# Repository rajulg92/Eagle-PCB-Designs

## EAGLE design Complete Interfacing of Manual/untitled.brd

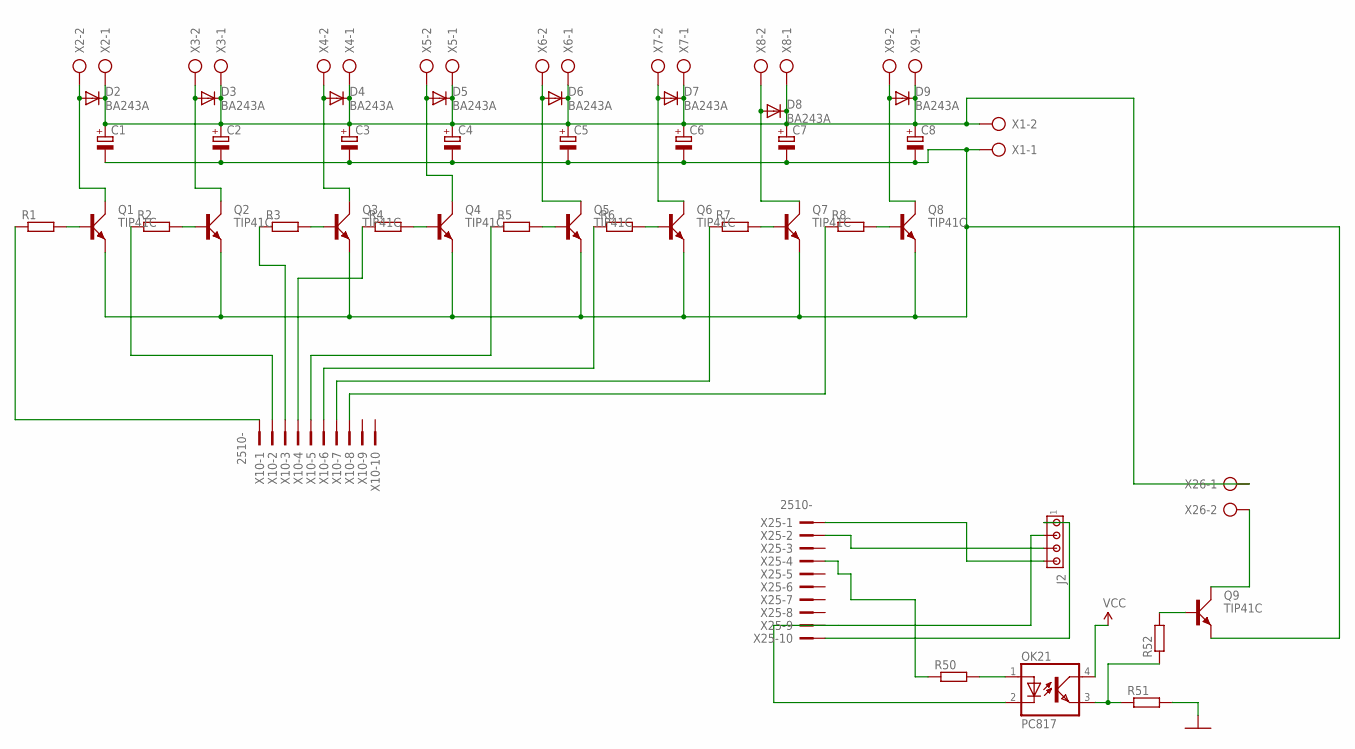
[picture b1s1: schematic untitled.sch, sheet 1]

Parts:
C1, C2, C3, C4, C5, C6, C7, C8: CPOL-EUE5-10.5; E5-10,5
D2, D3, D4, D5, D6, D7, D8, D9: BA243A; DO35-10
J2: MTA04-100; 10X04MTA
OK21: PC817; DIL04
Q1, Q2, Q3, Q4, Q5, Q6, Q7, Q8, Q9: TIP41C; TO220AV
R1, R2, R3, R4, R5, R6, R7, R8, R50, R51, R52: R-EU_0204/7; 0204/7
X1, X2, X3, X4, X5, X6, X7, X8, X9, X26: AK300/2
X10, X25: 2510-; PAK100/2500-10

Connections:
GND: R51.2; also elsewhere on the board
unnamed: Q1.B, R1.2
unnamed: Q2.B, R2.2
unnamed: Q3.B, R3.2
unnamed: Q4.B, R4.2
unnamed: Q5.B, R5.2
unnamed: Q7.B, R7.2
unnamed: Q8.B, R8.2
unnamed: Q6.B, R6.2
unnamed: D2.A, Q1.C, X2.2
unnamed: D3.A, Q2.C, X3.2
unnamed: D4.A, Q3.C, X4.2
unnamed: D5.A, Q4.C, X5.2
unnamed: D6.A, Q5.C, X6.2
unnamed: D7.A, Q6.C, X7.2
unnamed: D8.A, Q7.C, X8.2
unnamed: D9.A, Q8.C, X9.2
unnamed: C1.+, C2.+, C3.+, C4.+, C5.+, C6.+, C7.+, C8.+, D2.C, D3.C, D4.C, D5.C, D6.C, D7.C, D8.C, D9.C, X1.2, X2.1, X3.1, X4.1, X5.1, X6.1, X7.1, X8.1, X9.1, X26.1
unnamed: R3.1, X10.3
unnamed: R4.1, X10.4
unnamed: R1.1, X10.1
unnamed: R2.1, X10.2
unnamed: R5.1, X10.5
unnamed: R6.1, X10.6
unnamed: R7.1, X10.7
unnamed: R8.1, X10.8
unnamed: J2.1, X25.10
unnamed: J2.2, OK21.2 (C), X25.9
unnamed: J2.3, X25.2
unnamed: J2.4, X25.1
unnamed: OK21.1 (A), R50.2
unnamed: R50.1, X25.4
unnamed: OK21.3 (EMIT), R51.1, R52.1
unnamed: Q9.B, R52.2
unnamed: Q9.C, X26.2
unnamed: C1.-, C2.-, C3.-, C4.-, C5.-, C6.-, C7.-, C8.-, Q1.E, Q2.E, Q3.E, Q4.E, Q5.E, Q6.E, Q7.E, Q8.E, Q9.E, X1.1
VCC: OK21.4 (COL); also elsewhere on the board

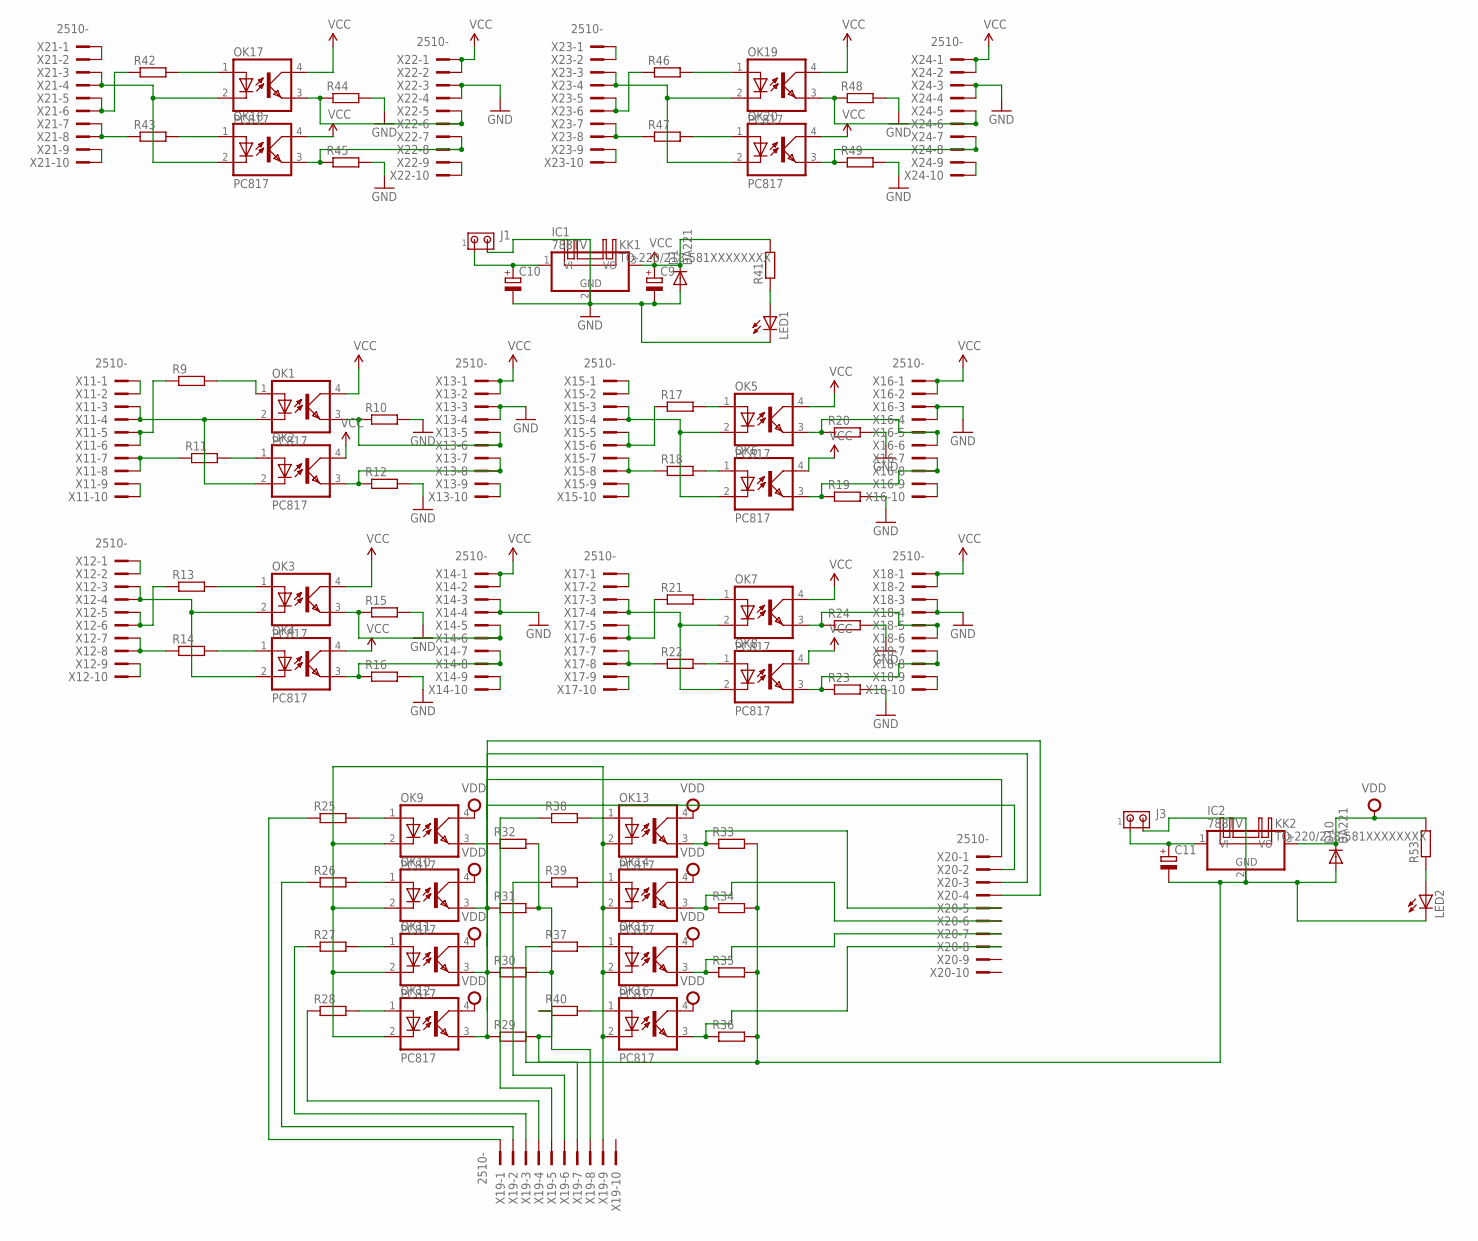
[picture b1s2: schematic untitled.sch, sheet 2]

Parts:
C9: CPOL-EUE5-10.5; E5-10,5
C10, C11: CPOL-EUE7.5-18; E7,5-18
D1, D10: BA221; DO35-10
IC1, IC2: 788TV; TO220V
J1, J3: MTA02-156; 1X2MTA
KK1, KK2: TO-220/218-581XXXXXXXX; 581XXXXXXXX
LED1, LED2: LEDSFH480; SFH480
OK1, OK2, OK3, OK4, OK5, OK6, OK7, OK8, OK9, OK10, OK11, OK12, OK13, OK14, OK15, OK16, OK17, OK18, OK19, OK20: PC817; DIL04; MPN PC817X4J000F
R9, R10, R11, R12, R13, R14, R15, R16, R17, R18, R19, R20, R21, R22, R23, R24, R25, R26, R27, R28, R29, R30, R31, R32, R33, R34, R35, R36, R37, R38, R39, R40, R41, R42, R43, R44, R45, R46, R47, R48, R49, R53: R-EU_0207/10; 0207/10
X11, X12, X13, X14, X15, X16, X17, X18, X19, X20, X21, X22, X23, X24: 2510-; PAK100/2500-10

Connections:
GND: C9.-, C10.-, D1.A, IC1.2 (GND), J1.2, LED1.K (C), R10.2, R12.2, R15.2, R16.2, R19.2, R20.2, R23.2, R24.2, R44.2, R45.2, R48.2, R49.2, X13.3, X13.4, X14.3, X14.4, X16.3, X16.4, X18.3, X18.4, X22.3, X22.4, X24.3, X24.4; also elsewhere on the board
unnamed: X11.1, X11.2
unnamed: R9.1, X11.5, X11.6
unnamed: R11.1, X11.7, X11.8
unnamed: X11.9, X11.10
unnamed: X12.1, X12.2
unnamed: R13.1, X12.5, X12.6
unnamed: R14.1, X12.7, X12.8
unnamed: X12.9, X12.10
unnamed: OK1.1 (A), R9.2
unnamed: OK2.1 (A), R11.2
unnamed: OK1.2 (C), OK2.2 (C), X11.3, X11.4
unnamed: OK2.3 (EMIT), R12.1, X13.7, X13.8
unnamed: X13.9, X13.10
unnamed: OK3.1 (A), R13.2
unnamed: OK4.1 (A), R14.2
unnamed: OK3.2 (C), OK4.2 (C), X12.3, X12.4
unnamed: OK3.3 (EMIT), R15.1, X14.5, X14.6
unnamed: OK4.3 (EMIT), R16.1, X14.7, X14.8
unnamed: X14.9, X14.10
unnamed: OK5.1 (A), R17.2
unnamed: OK6.1 (A), R18.2
unnamed: X15.1, X15.2
unnamed: R17.1, X15.5, X15.6
unnamed: R18.1, X15.7, X15.8
unnamed: X15.9, X15.10
unnamed: OK5.2 (C), OK6.2 (C), X15.3, X15.4
unnamed: OK5.3 (EMIT), R20.1, X16.5, X16.6
unnamed: OK6.3 (EMIT), R19.1, X16.7, X16.8
unnamed: X16.9, X16.10
unnamed: OK7.1 (A), R21.2
unnamed: OK8.1 (A), R22.2
unnamed: X17.1, X17.2
unnamed: R21.1, X17.5, X17.6
unnamed: R22.1, X17.7, X17.8
unnamed: X17.9, X17.10
unnamed: OK7.2 (C), OK8.2 (C), X17.3, X17.4
unnamed: OK7.3 (EMIT), R24.1, X18.5, X18.6
unnamed: OK8.3 (EMIT), R23.1, X18.7, X18.8
unnamed: X18.9, X18.10
unnamed: R25.1, X19.1
unnamed: OK9.1 (A), R25.2
unnamed: R26.1, X19.2
unnamed: R27.1, X19.3
unnamed: R28.1, X19.4
unnamed: OK12.1 (A), R28.2
unnamed: OK11.1 (A), R27.2
unnamed: OK10.1 (A), R26.2
unnamed: OK9.2 (C), OK10.2 (C), OK11.2 (C), OK12.2 (C), OK13.2 (C), OK14.2 (C), OK15.2 (C), OK16.2 (C), X19.9
unnamed: OK10.3 (EMIT), R31.1, X20.2
unnamed: OK11.3 (EMIT), R30.1, X20.3
unnamed: OK12.3 (EMIT), R29.1, X20.4
unnamed: OK13.1 (A), R38.2
unnamed: OK14.1 (A), R39.2
unnamed: OK15.1 (A), R37.2
unnamed: OK16.1 (A), R40.2
unnamed: R38.1, X19.5
unnamed: R39.1, X19.6
unnamed: R37.1, X19.7
unnamed: R40.1, X19.8
unnamed: OK15.3 (EMIT), R35.1, X20.7
unnamed: OK16.3 (EMIT), R36.1, X20.8
unnamed: OK14.3 (EMIT), R34.1, X20.6
unnamed: OK13.3 (EMIT), R33.1, X20.5
unnamed: C10.+, IC1.1 (VI), J1.1
unnamed: LED1.A, R41.1
unnamed: OK1.3 (EMIT), R10.1, X13.5, X13.6
unnamed: X21.1, X21.2
unnamed: R42.1, X21.5, X21.6
unnamed: R43.1, X21.7, X21.8
unnamed: X21.9, X21.10
unnamed: OK17.1 (A), R42.2
unnamed: OK18.1 (A), R43.2
unnamed: OK17.2 (C), OK18.2 (C), X21.3, X21.4
unnamed: OK17.3 (EMIT), R44.1, X22.5, X22.6
unnamed: OK18.3 (EMIT), R45.1, X22.7, X22.8
unnamed: X22.9, X22.10
unnamed: X23.1, X23.2
unnamed: R46.1, X23.5, X23.6
unnamed: R47.1, X23.7, X23.8
unnamed: X23.9, X23.10
unnamed: OK19.1 (A), R46.2
unnamed: OK20.1 (A), R47.2
unnamed: OK19.2 (C), OK20.2 (C), X23.3, X23.4
unnamed: OK19.3 (EMIT), R48.1, X24.5, X24.6
unnamed: OK20.3 (EMIT), R49.1, X24.7, X24.8
unnamed: X24.9, X24.10
unnamed: C11.+, IC2.1 (VI), J3.1
unnamed: LED2.A, R53.1
unnamed: OK9.3 (EMIT), R32.1
unnamed: C11.-, D10.A, IC2.2 (GND), J3.2, LED2.K (C), R29.2, R30.2, R31.2, R32.2, R33.2, R34.2, R35.2, R36.2
VCC: C9.+, D1.C, IC1.3 (VO), OK1.4 (COL), OK2.4 (COL), OK3.4 (COL), OK4.4 (COL), OK5.4 (COL), OK6.4 (COL), OK7.4 (COL), OK8.4 (COL), OK17.4 (COL), OK18.4 (COL), OK19.4 (COL), OK20.4 (COL), R41.2, X13.1, X13.2, X14.1, X14.2, X16.1, X16.2, X18.1, X18.2, X22.1, X22.2, X24.1, X24.2; also elsewhere on the board
VDD: D10.C, IC2.3 (VO), OK9.4 (COL), OK10.4 (COL), OK11.4 (COL), OK12.4 (COL), OK13.4 (COL), OK14.4 (COL), OK15.4 (COL), OK16.4 (COL), R53.2

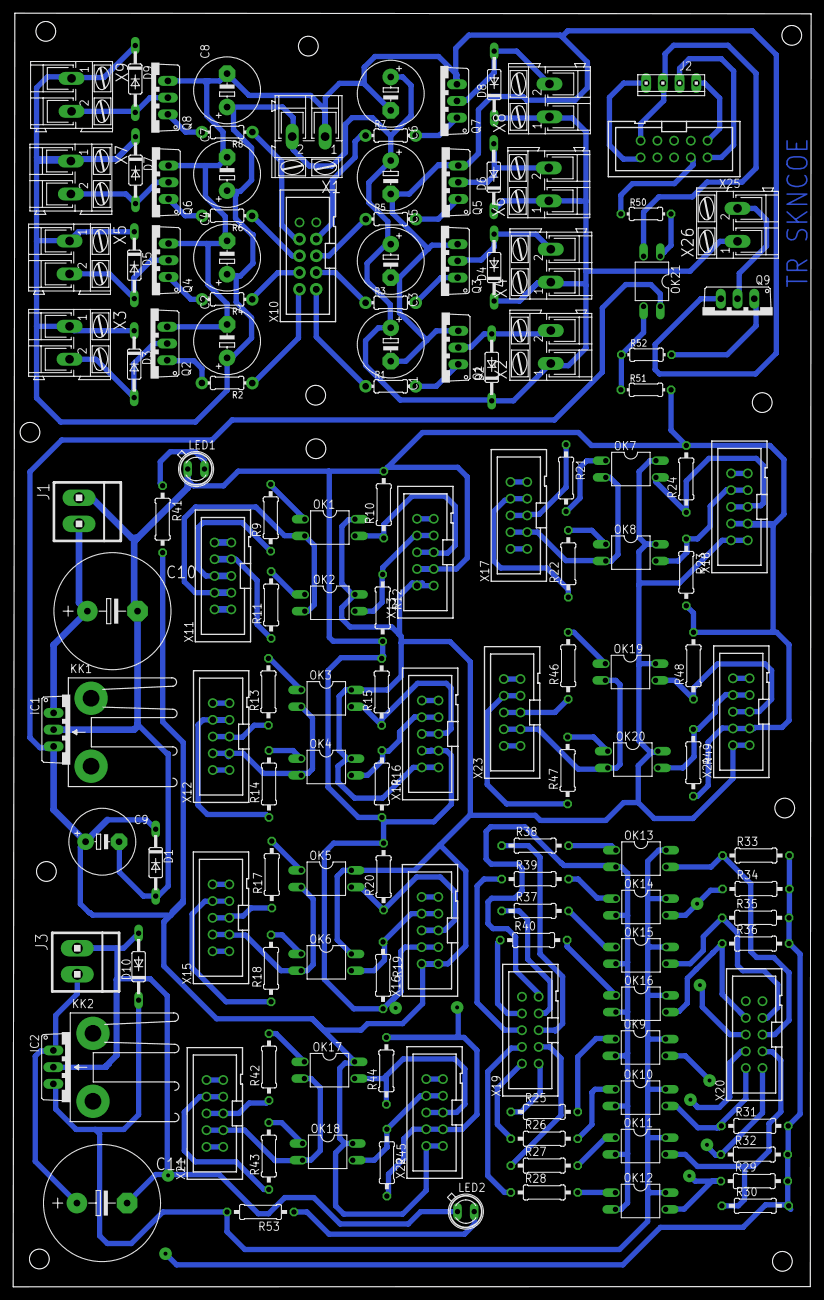
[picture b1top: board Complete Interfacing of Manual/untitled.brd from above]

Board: 2 copper layers, 121.2 x 193.5 mm, 139 parts (0 on the bottom side), 128 nets.

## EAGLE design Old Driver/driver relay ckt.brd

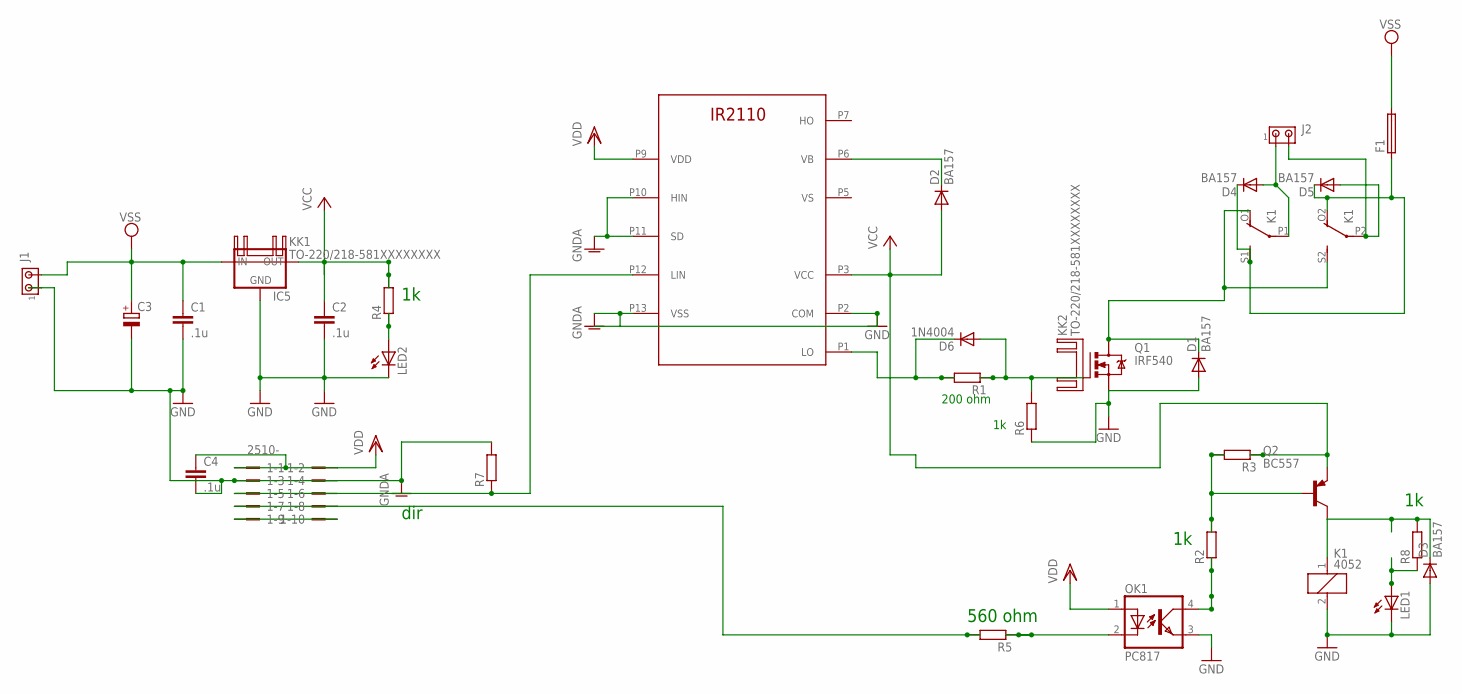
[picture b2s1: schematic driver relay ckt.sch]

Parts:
1: 2510-; PAK100/2500-10
C1, C2, C4: .1u; C2.5-3
C3: CPOL-EUE7.5-16; E7,5-16
D1, D2, D3, D4, D5: BA157; P1-10
D6: 1N4004; DO41-10
F1: SH22,5A
IC5: 78XXS
J1, J2: MTA02-156; 1X2MTA
K1: 4052; F4052
KK1, KK2: TO-220/218-581XXXXXXXX; 581XXXXXXXX
LED1, LED2: LEDSFH482; SFH482
OK1: PC817; DIL04
Q1: IRF540; TO220BV
Q2: BC557; TO92-EBC
R1, R2, R3, R4, R5, R6, R7, R8: R-EU_0207/10; 0207/10
U$1: IR2110N; DIL14-1

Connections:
GND: C2.2, D1.A, D3.A, IC5.GND, K1.2, LED1.K (C), LED2.K (C), OK1.3 (EMIT), Q1.S, R6.1, U$1.P2 (COM), U$1.P13 (VSS)
GNDA: 1.3, 1.4, C1.2, C3.-, C4.2, J1.1, R7.2, U$1.P10 (HIN), U$1.P11 (SD)
unnamed: D6.C, R1.2, U$1.P1 (LO)
unnamed: D6.A, Q1.G, R1.1, R6.2
unnamed: D2.C, U$1.P6 (VB)
unnamed: LED1.A, R8.1
unnamed: D1.C, K1.O1 (O), K1.S2 (S), Q1.D
unnamed: 1.9, 1.10
unnamed: 1.5, 1.6, R7.1, U$1.P12 (LIN)
unnamed: 1.7, 1.8, R5.2
unnamed: C2.1, D2.A, IC5.OUT, Q2.E, R3.1, R4.2, U$1.P3 (VCC)
unnamed: D5.A, J2.2, K1.P2
unnamed: D4.C, D5.C, F1.1, K1.O2 (O), K1.S1 (S)
unnamed: D3.C, K1.1, Q2.C, R8.2
unnamed: Q2.B, R2.2, R3.2
unnamed: OK1.4 (COL), R2.1
unnamed: LED2.A, R4.1
unnamed: OK1.2 (C), R5.1
unnamed: D4.A, J2.1, K1.P1
VDD: 1.1, 1.2, C4.1, OK1.1 (A), U$1.P9 (VDD)
VSS: C1.1, C3.+, F1.2, IC5.IN, J1.2

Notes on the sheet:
dir
560 ohm
200 ohm

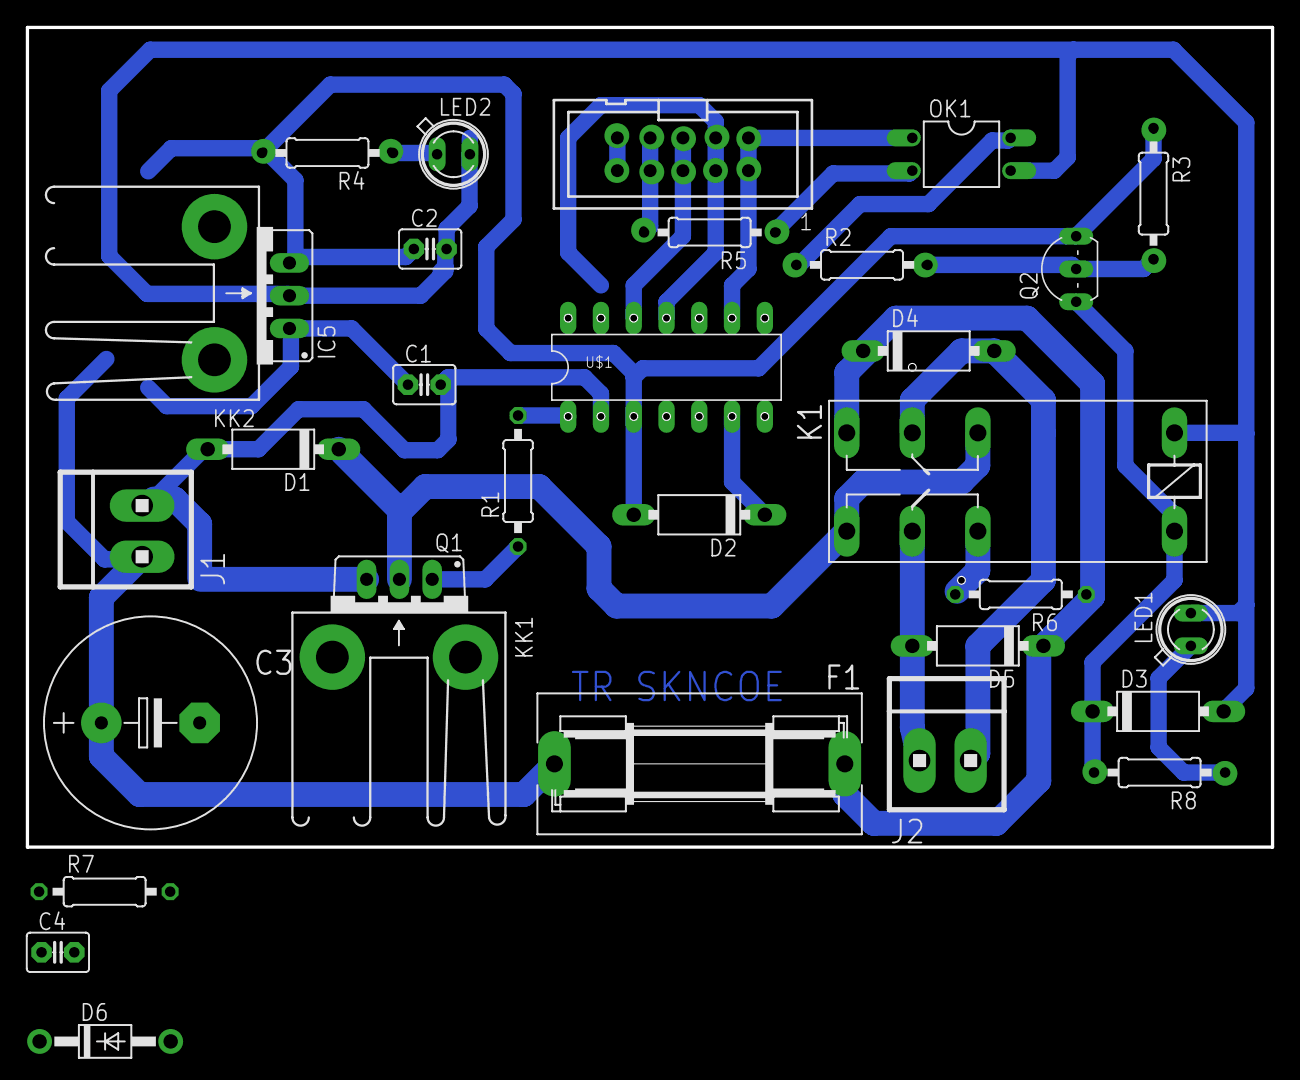
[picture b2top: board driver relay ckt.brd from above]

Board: 2 copper layers, 96.5 x 63.5 mm, 32 parts (0 on the bottom side), 21 nets.

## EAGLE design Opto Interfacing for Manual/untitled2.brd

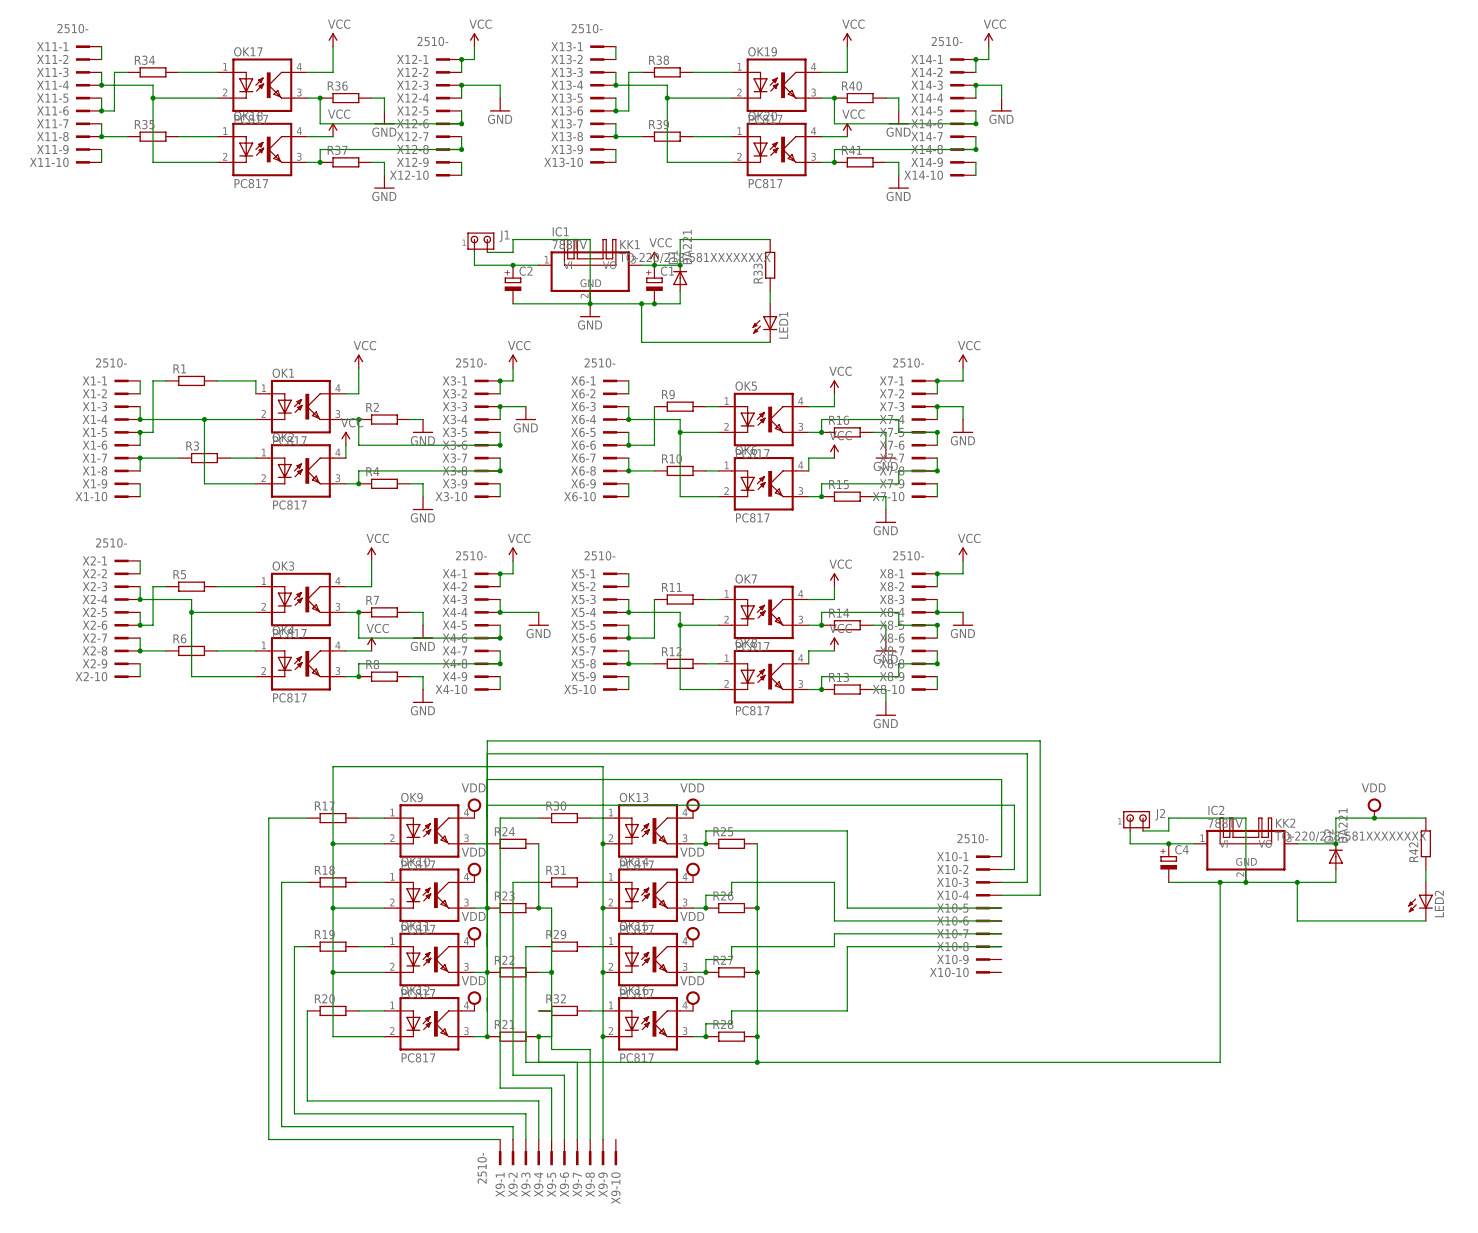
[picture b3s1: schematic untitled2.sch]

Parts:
C1: CPOL-EUE5-10.5; E5-10,5
C2, C4: CPOL-EUE7.5-18; E7,5-18
D1, D2: BA221; DO35-10
IC1, IC2: 788TV; TO220V
J1, J2: MTA02-156; 1X2MTA
KK1, KK2: TO-220/218-581XXXXXXXX; 581XXXXXXXX
LED1, LED2: LEDSFH480; SFH480
OK1, OK2, OK3, OK4, OK5, OK6, OK7, OK8, OK9, OK10, OK11, OK12, OK13, OK14, OK15, OK16, OK17, OK18, OK19, OK20: PC817; DIL04; MPN PC817X4J000F
R1, R2, R3, R4, R5, R6, R7, R8, R9, R10, R11, R12, R13, R14, R15, R16, R17, R18, R19, R20, R21, R22, R23, R24, R25, R26, R27, R28, R29, R30, R31, R32, R33, R34, R35, R36, R37, R38, R39, R40, R41, R42: R-EU_0207/10; 0207/10
X1, X2, X3, X4, X5, X6, X7, X8, X9, X10, X11, X12, X13, X14: 2510-; PAK100/2500-10

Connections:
GND: C1.-, C2.-, D1.A, IC1.2 (GND), J1.2, LED1.K (C), R2.2, R4.2, R7.2, R8.2, R13.2, R14.2, R15.2, R16.2, R36.2, R37.2, R40.2, R41.2, X3.3, X3.4, X4.3, X4.4, X7.3, X7.4, X8.3, X8.4, X12.3, X12.4, X14.3, X14.4
unnamed: X1.1, X1.2
unnamed: C2.+, IC1.1 (VI), J1.1
unnamed: R1.1, X1.5, X1.6
unnamed: R3.1, X1.7, X1.8
unnamed: X1.9, X1.10
unnamed: X2.1, X2.2
unnamed: OK5.3 (EMIT), R16.1, X7.5, X7.6
unnamed: R5.1, X2.5, X2.6
unnamed: R6.1, X2.7, X2.8
unnamed: X2.9, X2.10
unnamed: OK1.1 (A), R1.2
unnamed: OK3.1 (A), R5.2
unnamed: OK3.2 (C), OK4.2 (C), X2.3, X2.4
unnamed: OK2.1 (A), R3.2
unnamed: OK1.2 (C), OK2.2 (C), X1.3, X1.4
unnamed: C4.+, IC2.1 (VI), J2.1
unnamed: LED2.A, R42.1
unnamed: OK1.3 (EMIT), R2.1, X3.5, X3.6
unnamed: OK2.3 (EMIT), R4.1, X3.7, X3.8
unnamed: X3.9, X3.10
unnamed: OK4.1 (A), R6.2
unnamed: OK6.3 (EMIT), R15.1, X7.7, X7.8
unnamed: OK3.3 (EMIT), R7.1, X4.5, X4.6
unnamed: OK4.3 (EMIT), R8.1, X4.7, X4.8
unnamed: X4.9, X4.10
unnamed: OK5.1 (A), R9.2
unnamed: OK6.1 (A), R10.2
unnamed: X6.1, X6.2
unnamed: R9.1, X6.5, X6.6
unnamed: R10.1, X6.7, X6.8
unnamed: X6.9, X6.10
unnamed: OK7.1 (A), R11.2
unnamed: OK5.2 (C), OK6.2 (C), X6.3, X6.4
unnamed: OK8.1 (A), R12.2
unnamed: X7.9, X7.10
unnamed: X5.1, X5.2
unnamed: R11.1, X5.5, X5.6
unnamed: R12.1, X5.7, X5.8
unnamed: X5.9, X5.10
unnamed: OK7.2 (C), OK8.2 (C), X5.3, X5.4
unnamed: OK7.3 (EMIT), R14.1, X8.5, X8.6
unnamed: OK8.3 (EMIT), R13.1, X8.7, X8.8
unnamed: C4.-, D2.A, IC2.2 (GND), J2.2, LED2.K (C), R21.2, R22.2, R23.2, R24.2, R25.2, R26.2, R27.2, R28.2
unnamed: X8.9, X8.10
unnamed: R17.1, X9.1
unnamed: OK9.1 (A), R17.2
unnamed: R18.1, X9.2
unnamed: R19.1, X9.3
unnamed: R20.1, X9.4
unnamed: OK12.1 (A), R20.2
unnamed: OK11.1 (A), R19.2
unnamed: OK10.1 (A), R18.2
unnamed: OK9.2 (C), OK10.2 (C), OK11.2 (C), OK12.2 (C), OK13.2 (C), OK14.2 (C), OK15.2 (C), OK16.2 (C), X9.9
unnamed: OK10.3 (EMIT), R23.1, X10.2
unnamed: OK11.3 (EMIT), R22.1, X10.3
unnamed: OK12.3 (EMIT), R21.1, X10.4
unnamed: OK13.1 (A), R30.2
unnamed: OK14.1 (A), R31.2
unnamed: OK15.1 (A), R29.2
unnamed: OK16.1 (A), R32.2
unnamed: R30.1, X9.5
unnamed: R31.1, X9.6
unnamed: R29.1, X9.7
unnamed: R32.1, X9.8
unnamed: LED1.A, R33.1
unnamed: OK15.3 (EMIT), R27.1, X10.7
unnamed: OK16.3 (EMIT), R28.1, X10.8
unnamed: OK14.3 (EMIT), R26.1, X10.6
unnamed: OK13.3 (EMIT), R25.1, X10.5
unnamed: X11.1, X11.2
unnamed: R34.1, X11.5, X11.6
unnamed: R35.1, X11.7, X11.8
unnamed: X11.9, X11.10
unnamed: OK17.1 (A), R34.2
unnamed: OK18.1 (A), R35.2
unnamed: OK17.2 (C), OK18.2 (C), X11.3, X11.4
unnamed: OK17.3 (EMIT), R36.1, X12.5, X12.6
unnamed: OK18.3 (EMIT), R37.1, X12.7, X12.8
unnamed: X12.9, X12.10
unnamed: X13.1, X13.2
unnamed: R38.1, X13.5, X13.6
unnamed: R39.1, X13.7, X13.8
unnamed: X13.9, X13.10
unnamed: OK19.1 (A), R38.2
unnamed: OK20.1 (A), R39.2
unnamed: OK19.2 (C), OK20.2 (C), X13.3, X13.4
unnamed: OK19.3 (EMIT), R40.1, X14.5, X14.6
unnamed: OK20.3 (EMIT), R41.1, X14.7, X14.8
unnamed: X14.9, X14.10
unnamed: OK9.3 (EMIT), R24.1
VCC: C1.+, D1.C, IC1.3 (VO), OK1.4 (COL), OK2.4 (COL), OK3.4 (COL), OK4.4 (COL), OK5.4 (COL), OK6.4 (COL), OK7.4 (COL), OK8.4 (COL), OK17.4 (COL), OK18.4 (COL), OK19.4 (COL), OK20.4 (COL), R33.2, X3.1, X3.2, X4.1, X4.2, X7.1, X7.2, X8.1, X8.2, X12.1, X12.2, X14.1, X14.2
VDD: D2.C, IC2.3 (VO), OK9.4 (COL), OK10.4 (COL), OK11.4 (COL), OK12.4 (COL), OK13.4 (COL), OK14.4 (COL), OK15.4 (COL), OK16.4 (COL), R42.2

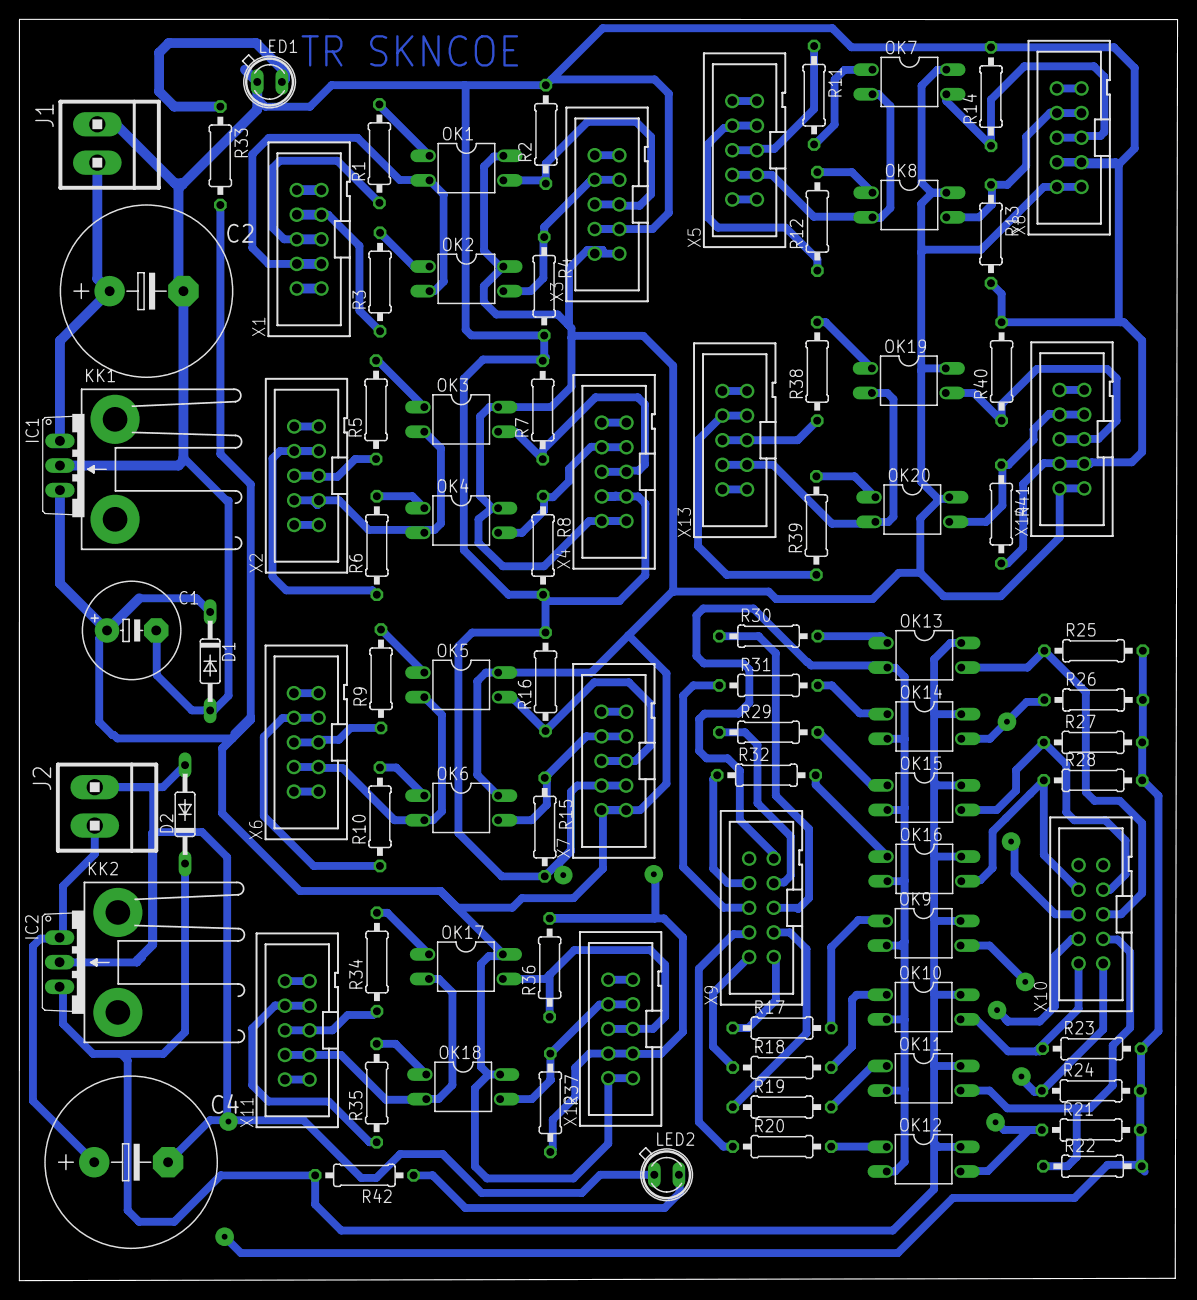
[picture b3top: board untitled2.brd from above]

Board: 2 copper layers, 119.5 x 130.2 mm, 89 parts (0 on the bottom side), 93 nets.

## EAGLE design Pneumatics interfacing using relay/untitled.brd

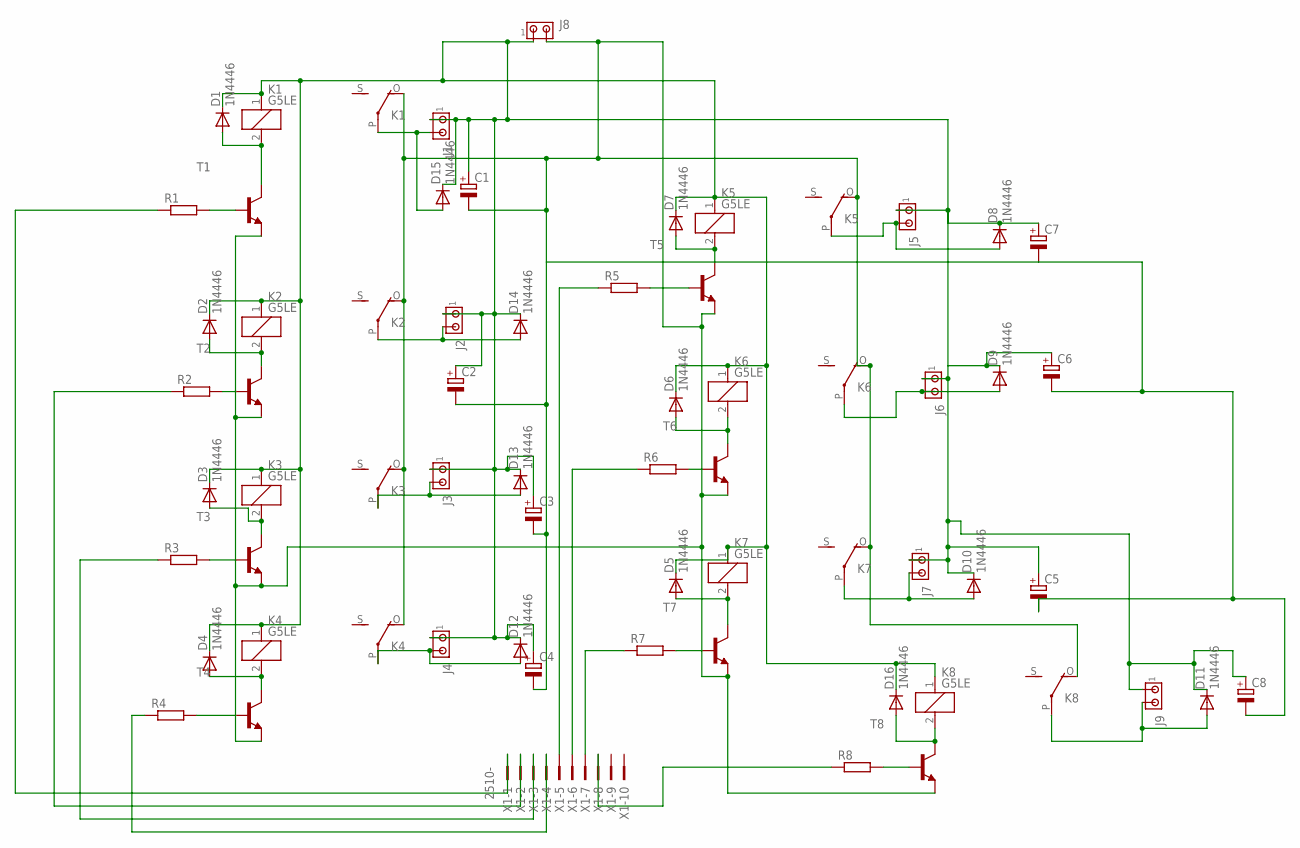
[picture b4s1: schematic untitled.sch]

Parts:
C1, C2, C3, C4, C5, C6, C7, C8: CPOL-EUE5-10.5; E5-10,5
D1, D2, D3, D4, D5, D6, D7, D8, D9, D10, D11, D12, D13, D14, D15, D16: 1N4446; DO35-10
J1, J2, J3, J4, J5, J6, J7, J8, J9: MTA02-156; 1X2MTA
K1, K2, K3, K4, K5, K6, K7, K8: G5LE
R1, R2, R3, R4, R5, R6, R7, R8: R-EU_0207/10; 0207/10
T1, T2, T3, T4, T5, T6, T7, T8: 2N5401-NPN-TO92-CBE; TO92-CBE
X1: 2510-; PAK100/2500-10

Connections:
unnamed: D4.A, K4.2, T4.C
unnamed: R4.2, T4.B
unnamed: R3.2, T3.B
unnamed: D3.A, K3.2, T3.C
unnamed: D2.A, K2.2, T2.C
unnamed: R2.2, T2.B
unnamed: D1.A, K1.2, T1.C
unnamed: R1.2, T1.B
unnamed: R5.2, T5.B
unnamed: D7.A, K5.2, T5.C
unnamed: R6.2, T6.B
unnamed: D6.A, K6.2, T6.C
unnamed: D5.A, K7.2, T7.C
unnamed: R7.2, T7.B
unnamed: R8.2, T8.B
unnamed: D11.A, J9.2, K8.P
unnamed: D14.A, J2.2, K2.P
unnamed: R1.1, X1.1
unnamed: R2.1, X1.2
unnamed: R3.1, X1.3
unnamed: R4.1, X1.4
unnamed: R7.1, X1.7
unnamed: R6.1, X1.6
unnamed: R5.1, X1.5
unnamed: D13.A, J3.2, K3.P
unnamed: D8.A, J5.2, K5.P
unnamed: D9.A, J6.2, K6.P
unnamed: D10.A, J7.2, K7.P
unnamed: D15.A, J1.2, K1.P
unnamed: D12.A, J4.2, K4.P
unnamed: D16.A, K8.2, T8.C
unnamed: C1.-, C2.-, C3.-, C4.-, C5.-, C6.-, C7.-, C8.-, J8.2, K1.O, K2.O, K3.O, K4.O, K5.O, K6.O, K7.O, K8.O, T1.E, T2.E, T3.E, T4.E, T5.E, T6.E, T7.E, T8.E
unnamed: R8.1, X1.8
unnamed: C1.+, C2.+, C3.+, C4.+, C5.+, C6.+, C7.+, C8.+, D1.C, D2.C, D3.C, D4.C, D5.C, D6.C, D7.C, D8.C, D9.C, D10.C, D11.C, D12.C, D13.C, D14.C, D15.C, D16.C, J1.1, J2.1, J3.1, J4.1, J5.1, J6.1, J7.1, J8.1, J9.1, K1.1, K2.1, K3.1, K4.1, K5.1, K6.1, K7.1, K8.1

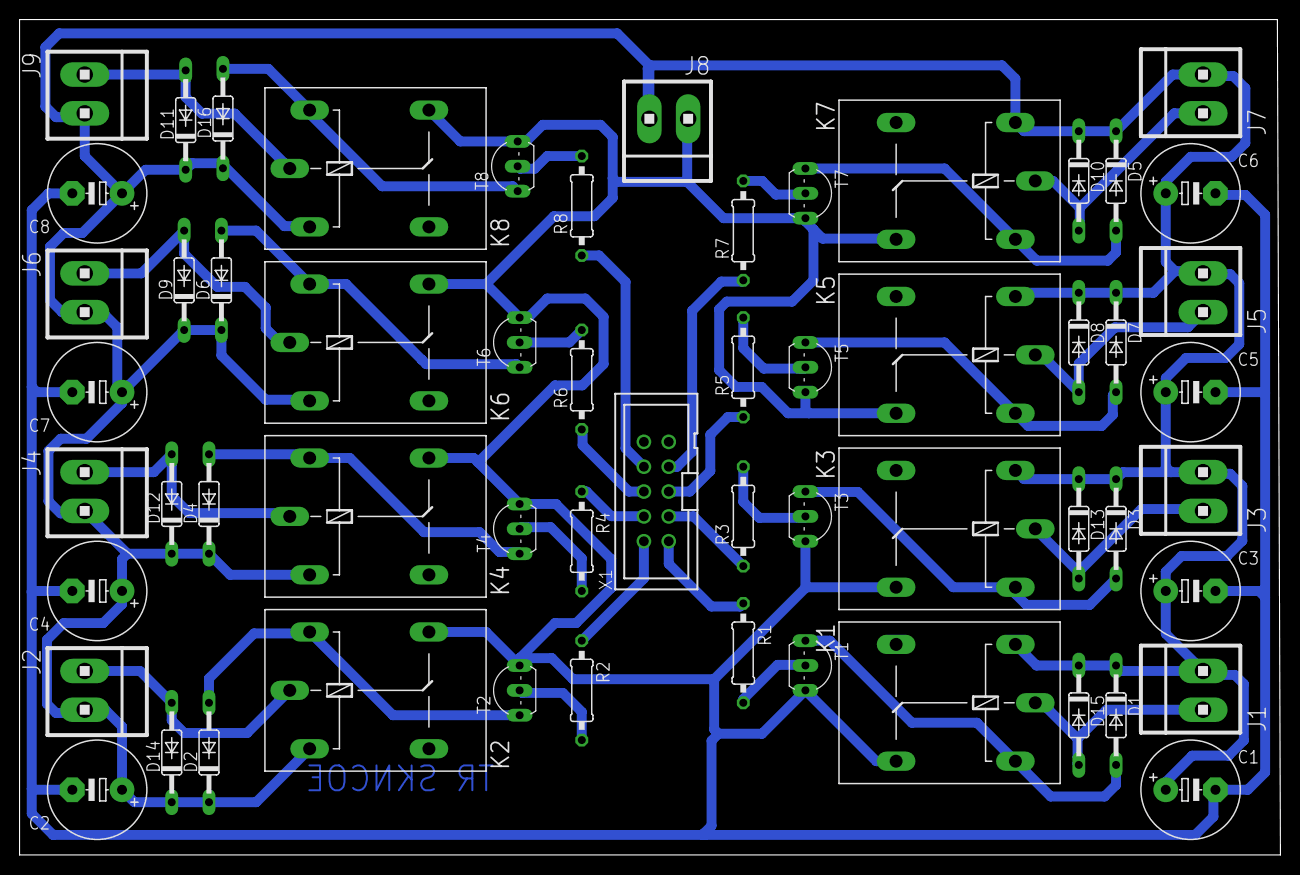
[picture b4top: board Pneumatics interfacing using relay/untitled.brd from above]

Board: 2 copper layers, 128.9 x 85.4 mm, 58 parts (0 on the bottom side), 34 nets.

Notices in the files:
parts and their libraries:
heatsink-aavid: Copyright (C) 2004, Bob Starr (bobstarr@mindspring.com)
